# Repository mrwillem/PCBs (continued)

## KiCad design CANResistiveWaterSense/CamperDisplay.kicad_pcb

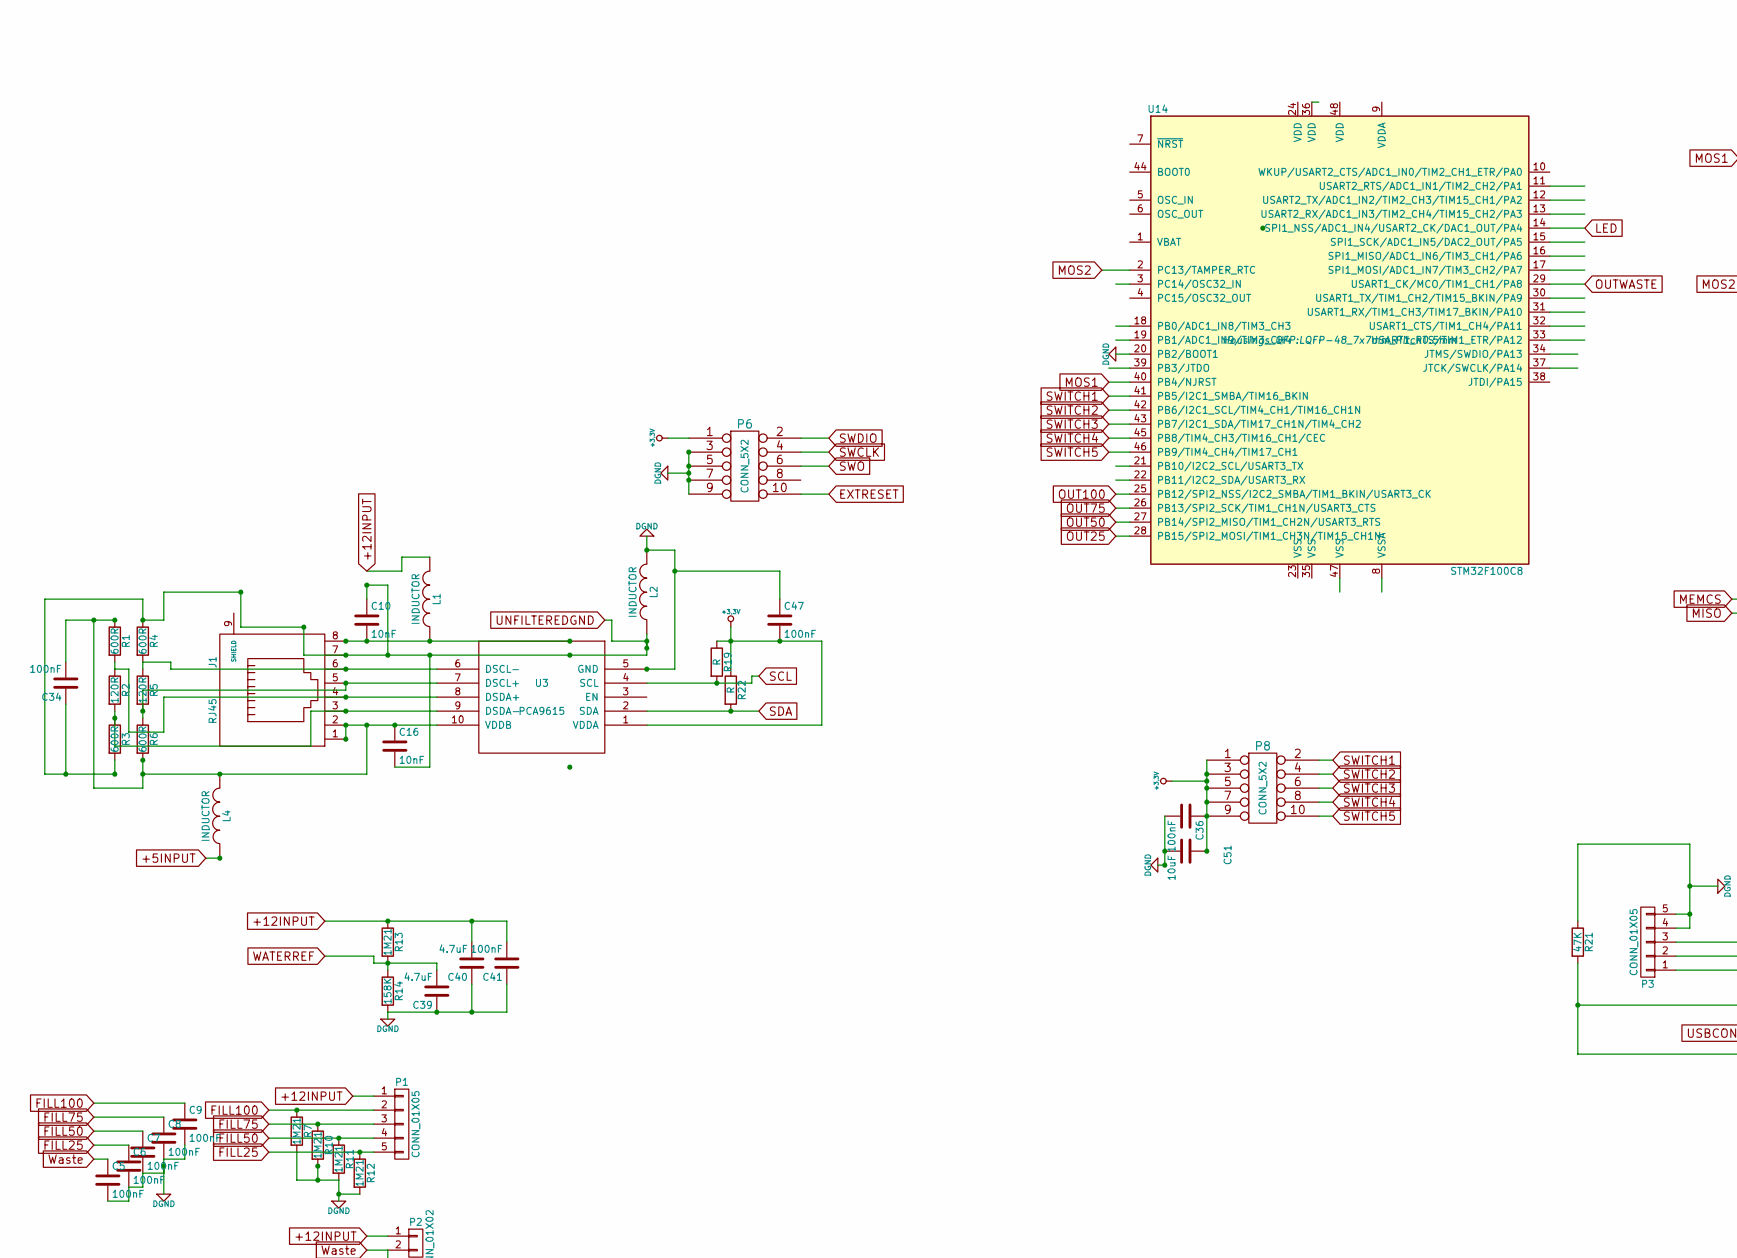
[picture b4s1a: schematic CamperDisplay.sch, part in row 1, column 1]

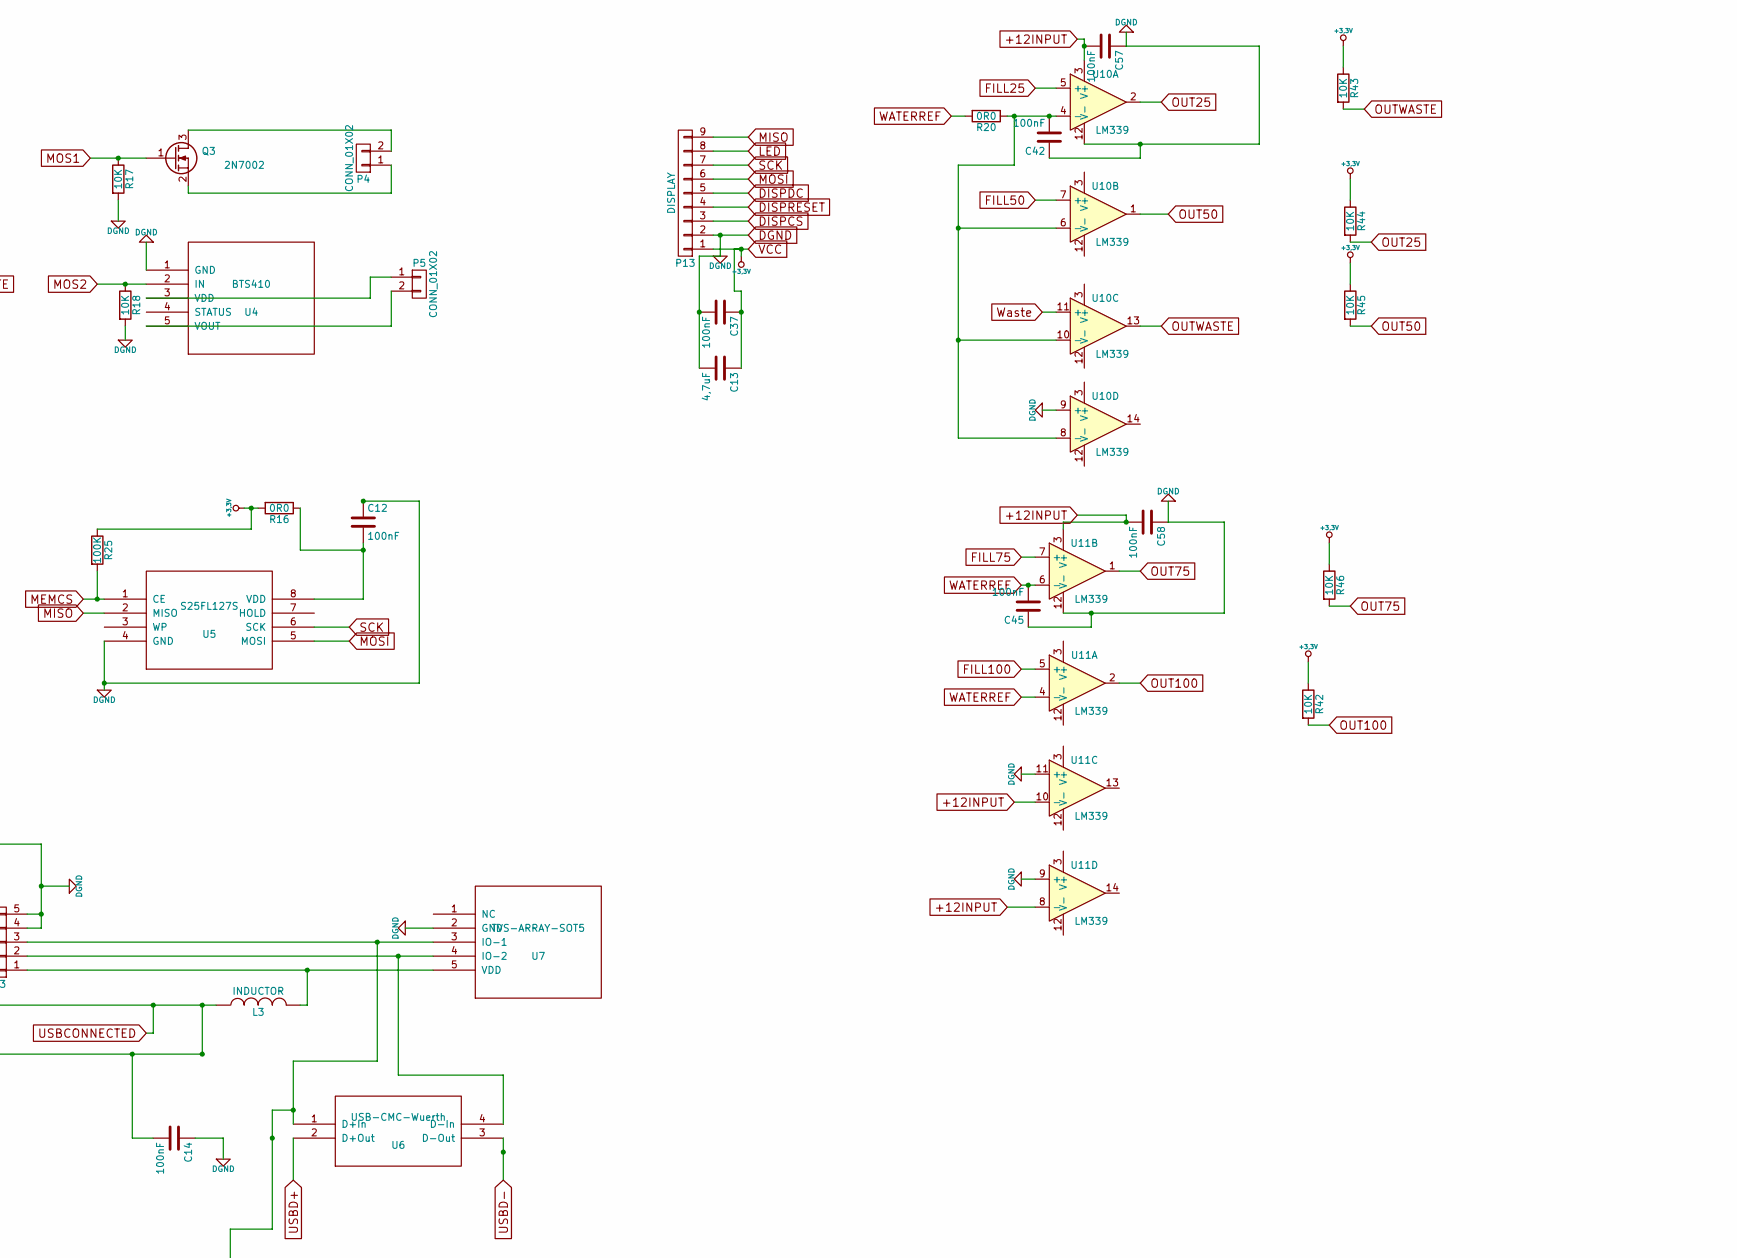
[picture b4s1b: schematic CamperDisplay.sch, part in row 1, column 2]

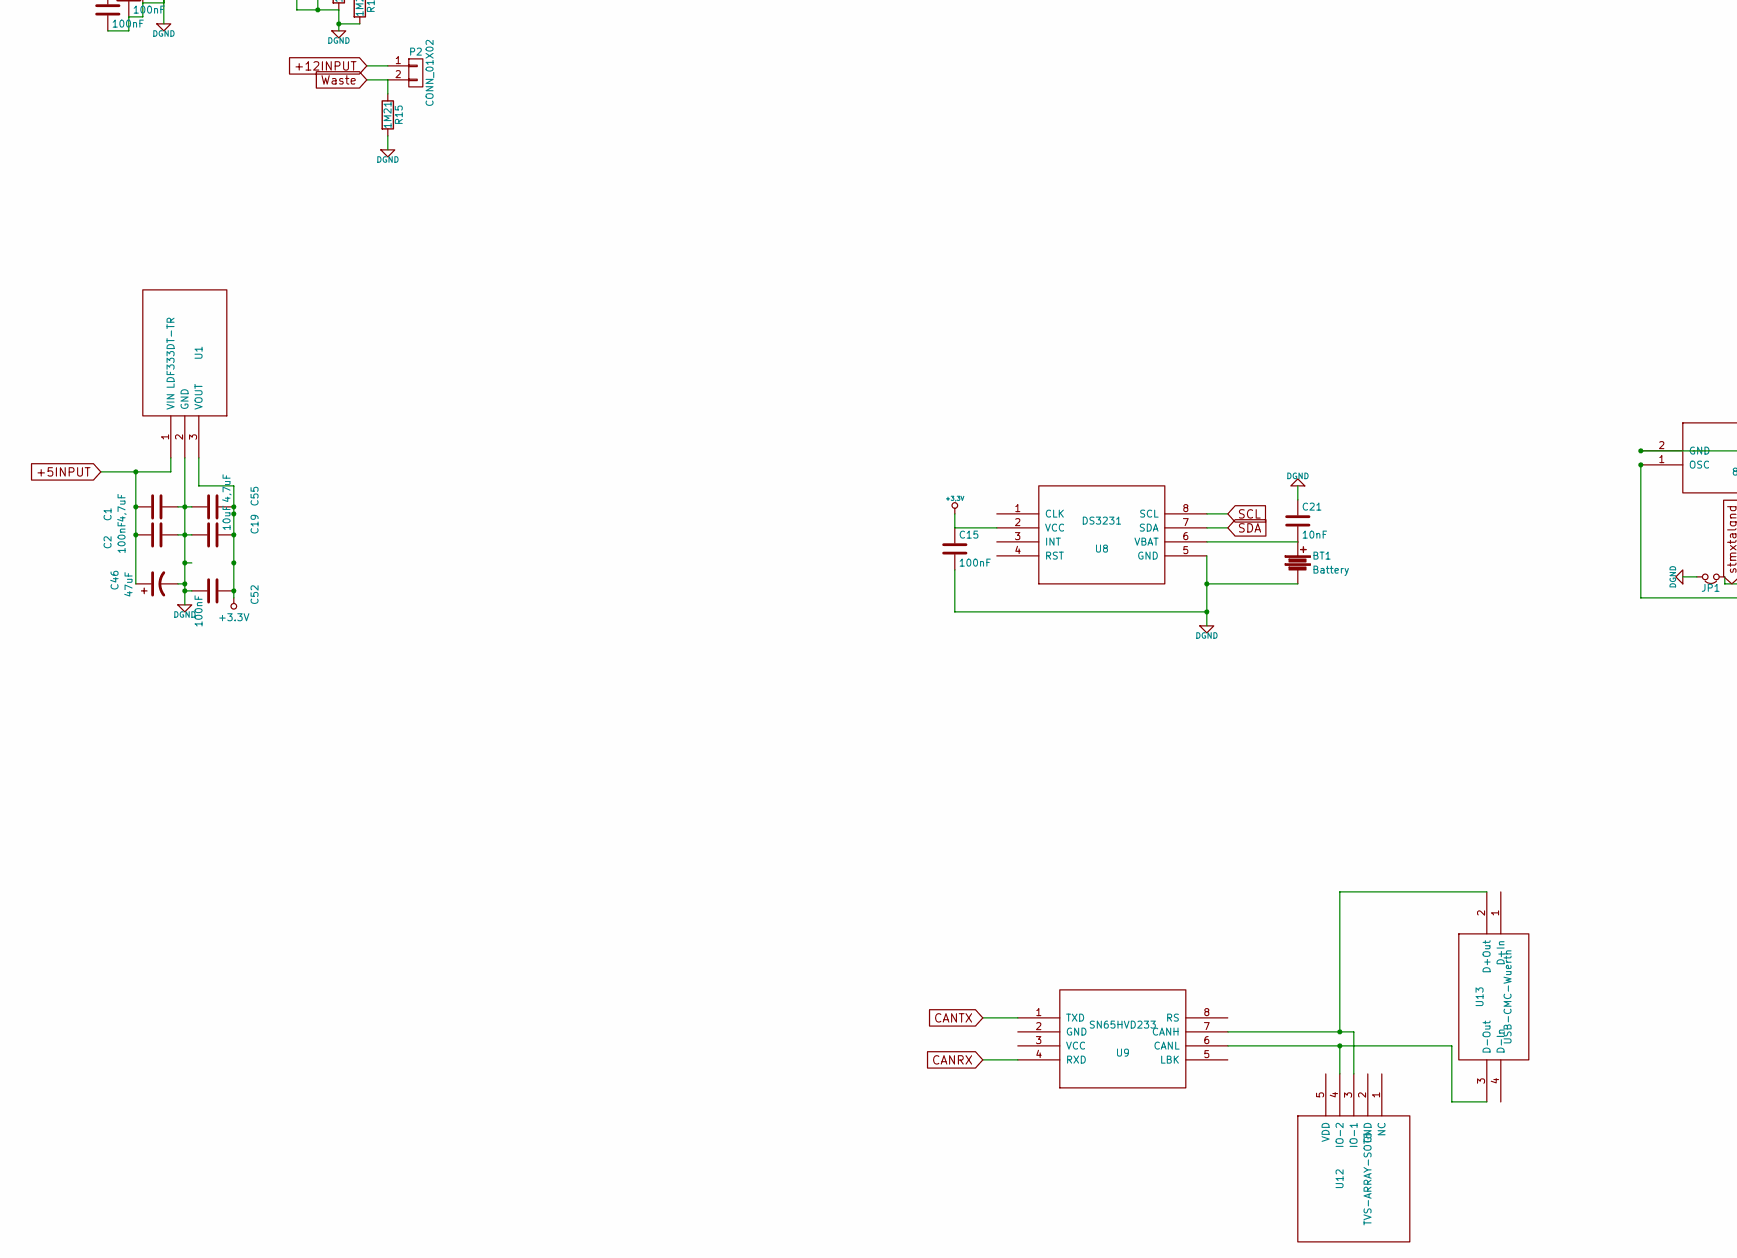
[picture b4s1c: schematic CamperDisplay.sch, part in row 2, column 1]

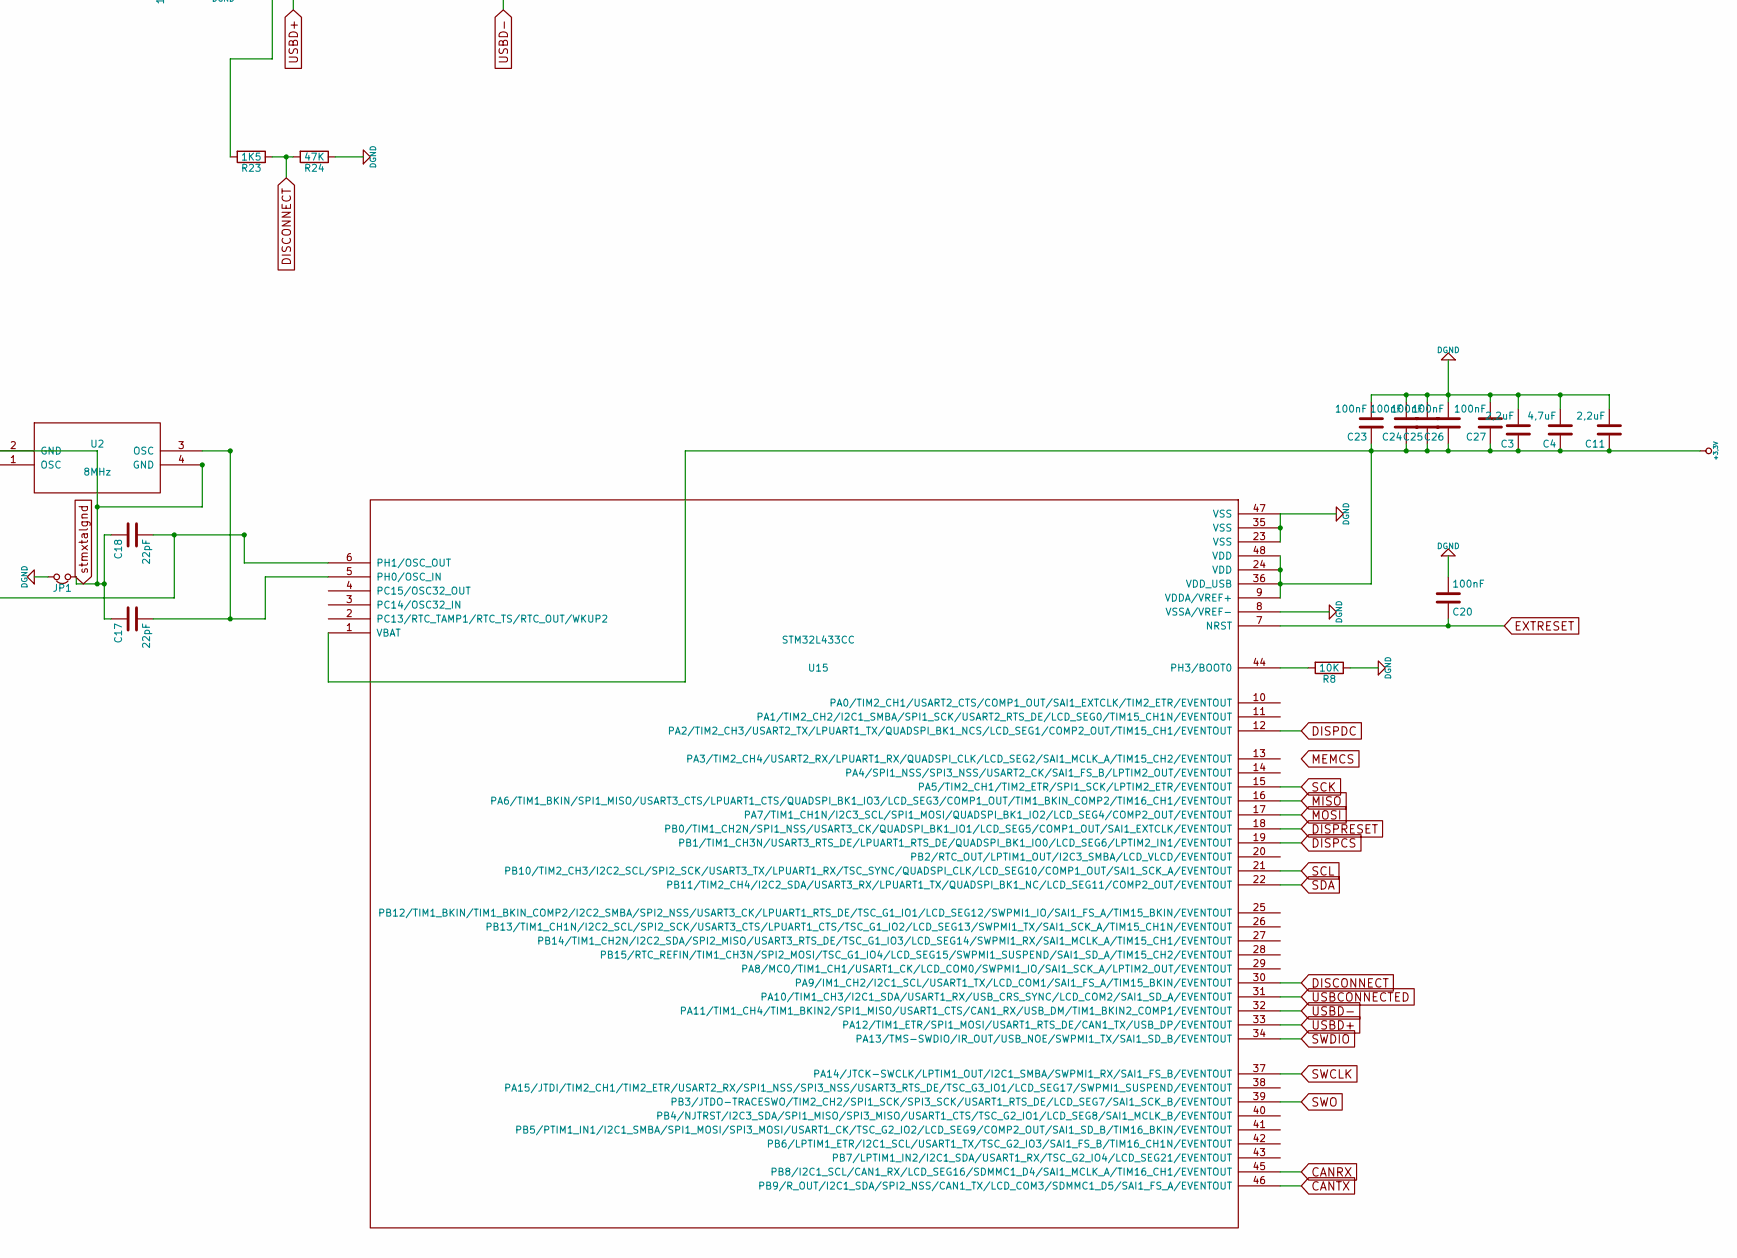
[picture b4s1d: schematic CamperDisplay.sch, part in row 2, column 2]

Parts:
BT1: Battery; BatterieHolderCR1025_SMD
C1, C4, C13, C55: 4,7uF; C_1206
C2, C5, C6, C7, C8, C9, C14, C15, C20, C23, C24, C25, C26, C27, C34, C36, C37, C41, C42, C45, C47, C52, C57, C58: 100nF; C_0805
C3: 2,2uF; C_0805
C10, C16, C21: 10nF; C_0805
C11: 2,2uF; C_1206
C12: 100nF; C_1206
C17, C18: 22pF; C_0805
C19, C51: 10uF; C_1206
C39, C40: 4.7uF; C_1206
C46: 47uF; c_elec_6.3x5.8
J1: RJ45; RJ45_8
JP1: Jumper_NC_Small; NetTie-I_Connected_SMD
L1, L2, L3, L4: INDUCTOR; C_0805_HandSoldering
P1: CONN_01X05; weidmueller_5
P2, P4, P5: CONN_01X02; weidmueller_2
P3: CONN_01X05; SMD_PIN_HEADER_01x05_angled
P6: CONN_5X2; Pin_Header_Straight_2x05_Pitch1.27mm
P8: CONN_5X2; weidmueller_10
P13: DISPLAY; 2.2inchQVGASPIwithStorage
Q3: 2N7002; SOT-23
R1, R3, R4, R6: 600R; R_0805_HandSoldering
R2, R5: 120R; R_0805_HandSoldering
R7, R10, R11, R12, R13, R15: 1M21; R_1206
R8, R17, R18, R42, R43, R44, R45, R46: 10K; R_0805_HandSoldering
R14: 158K; R_1206
R16, R20: 0R0; R_1206_HandSoldering
R19, R22: R; R_0805_HandSoldering
R21, R24: 47K; R_0603_HandSoldering
R23: 1K5; R_0603_HandSoldering
R25: 100K; R_0805_HandSoldering
U1: LDF333DT-TR; TO-252-2Lead
U2: 8MHz; Xtal_Ceramic_5x3.2
U3: PCA9615; TSSOP-10_3x3mm_Pitch0.5mm
U4: BTS410; TO-263-5Lead
U5: S25FL127S; SOIJ-8_5.3x5.3mm_Pitch1.27mm
U6, U13: USB-CMC-Wuerth; CMC-SMD-Wuerth
U7, U12: TVS-ARRAY-SOT5; SOT-23-5
U8: DS3231; SOIC-8_3.9x4.9mm_Pitch1.27mm
U9: SN65HVD233; SOIC-8_3.9x4.9mm_Pitch1.27mm
U10, U11: LM339; SOIC-14_3.9x8.7mm_Pitch1.27mm
U14: STM32F100C8; LQFP-48_7x7mm_Pitch0.5mm
U15: STM32L433CC; LQFP-48_7x7mm_Pitch0.5mm

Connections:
+5INPUT: C1.2, C2.2, C46.1, L4.1, U1.1 (VIN)
+12INPUT: C40.2, C41.2, C57.2, C58.2, L1.2, P1.1, P2.1, R13.1, U10.3 (V+), U11.3 (V+), U11.8 (-), U11.10 (-)
CANRX: U9.4 (RXD), U15.45 (PB8/I2C1_SCL/CAN1_RX/LCD_SEG16/SDMMC1_D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)
CANTX: U9.1 (TXD), U15.46 (PB9/R_OUT/I2C1_SDA/SPI2_NSS/CAN1_TX/LCD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)
DGND: BT1.2, C1.1, C2.1, C3.2, C4.2, C5.2, C6.2, C7.2, C8.2, C9.2, C11.2, C12.1, C13.2, C14.1, C15.2, C19.1, C20.2, C21.1, C23.2, C24.2, C25.2, C26.2, C27.2, C36.2, C37.2, C39.1, C40.1, C41.1, C42.1, C45.1, C46.2, C47.1, C51.2, C52.2, C55.1, C57.1, C58.1, JP1.1, L2.2, P3.4, P3.5, P6.3, P6.5, P6.7, P6.9, P13.2, R7.2, R8.1, R10.2, R11.2, R12.2, R14.2, R15.2, R17.2, R18.2, R21.1, R24.1, U1.2 (GND), U3.5 (GND), U4.1 (GND), U5.4 (GND), U7.2 (GND), U8.5 (GND), U10.9 (+), U10.12 (V-), U11.9 (+), U11.11 (+), U11.12 (V-), U14.20 (PB2/BOOT1), U15.8 (VSSA/VREF-), U15.23 (VSS), U15.35 (VSS), U15.47 (VSS)
DISCONNECT: R23.1, R24.2, U15.30 (PA9/IM1_CH2/I2C1_SCL/USART1_TX/LCD_COM1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)
DISPCS: P13.3, U15.19 (PB1/TIM1_CH3N/USART3_RTS_DE/LPUART1_RTS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)
DISPDC: P13.5, U15.12 (PA2/TIM2_CH3/USART2_TX/LPUART1_TX/QUADS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)
DISPRESET: P13.4, U15.18 (PB0/TIM1_CH2N/SPI1_NSS/USART3_CK/QUADSP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)
EXTRESET: C20.1, P6.10, U15.7 (NRST)
FILL25: C6.1, P1.5, R12.1, U10.5 (+)
FILL50: C7.1, P1.4, R11.1, U10.7 (+)
FILL75: C8.1, P1.3, R10.1, U11.7 (+)
FILL100: C9.1, P1.2, R7.1, U11.5 (+)
LED: P13.8, U14.14 (SPI1_NSS/ADC1_IN4/USART2_CK/DAC1_OUT/PA4)
MEMCS: R25.2, U5.1 (CE)
MISO: P13.9, U5.2 (MISO), U15.16 (PA6/TIM1_BKIN/SPI1_MISO/USART3_CTS/LPUA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)
MOS1: Q3.1 (G), R17.1, U14.40 (PB4/NJRST)
MOS2: R18.1, U4.2 (IN), U14.2 (PC13/TAMPER_RTC)
MOSI: P13.6, U5.5 (MOSI), U15.17 (PA7/TIM1_CH1N/I2C3_SCL/SPI1_MOSI/QUADSP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)
unnamed: BT1.1, C21.2, U8.6 (VBAT)
unnamed: C10.2, J1.8, L1.1
unnamed: C12.2, R16.1, U5.8 (VDD)
unnamed: C16.1, C34.2, J1.1, J1.2, L4.2, R1.1, R6.2, U3.10 (VDDB)
unnamed: C17.2, U2.3 (OSC), U15.5 (PH0/OSC_IN)
unnamed 25: C18.2, U2.1 (OSC), U15.6 (PH1/OSC_OUT); also elsewhere on the board
unnamed: C42.2, R20.1, U10.4 (-), U10.6 (-), U10.8 (-), U10.10 (-)
unnamed: J1.3, R2.2, R3.1, U3.9 (DSDA-)
unnamed: J1.4, R1.2, R2.1, U3.8 (DSDA+)
unnamed: J1.5, R5.2, R6.1, U3.7 (DSCL+)
unnamed: J1.6, R4.2, R5.1, U3.6 (DSCL-)
unnamed: L3.2, P3.1, U7.5 (VDD)
unnamed: P3.2, U6.4 (D-In), U7.4 (IO-2)
unnamed: P3.3, R23.2, U6.1 (D+In), U7.3 (IO-1)
unnamed: P4.1, Q3.2 (S)
unnamed: P4.2, Q3.3 (D)
unnamed: P5.1, U4.3 (VDD)
unnamed: P5.2, U4.5 (VOUT)
unnamed: R8.2, U15.44 (PH3/BOOT0)
unnamed: U9.7 (CANH), U12.3 (IO-1), U13.2 (D+Out)
unnamed: U9.6 (CANL), U12.4 (IO-2), U13.3 (D-Out)
OUT25: R44.2, U10.2, U14.28 (PB15/SPI2_MOSI/TIM1_CH3N/TIM15_CH1N)
OUT50: R45.2, U10.1, U14.27 (PB14/SPI2_MISO/TIM1_CH2N/USART3_RTS)
OUT75: R46.2, U11.1, U14.26 (PB13/SPI2_SCK/TIM1_CH1N/USART3_CTS)
OUT100: R42.2, U11.2, U14.25 (PB12/SPI2_NSS/I2C2_SMBA/TIM1_BKIN/USART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)
OUTWASTE: R43.2, U10.13, U14.29 (USART1_CK/MCO/TIM1_CH1/PA8)
SCK: P13.7, U5.6 (SCK), U15.15 (PA5/TIM2_CH1/TIM2_ETR/SPI1_SCK/LPTIM2_E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)
SCL: R19.2, U3.4 (SCL), U8.8 (SCL), U15.21 (PB10/TIM2_CH3/I2C2_SCL/SPI2_SCK/USART3_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)
SDA: R22.2, U3.2 (SDA), U8.7 (SDA), U15.22 (PB11/TIM2_CH4/I2C2_SDA/USART3_RX/LPUART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)
SWCLK: P6.4, U15.37 (PA14/JTCK-SWCLK/LPTIM1_OUT/I2C1_SMBA/SW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)
SWDIO: P6.2, U15.34 (PA13/TMS-SWDIO/IR_OUT/USB_NOE/SWPMI1_TX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)
SWITCH1: P8.2, U14.41 (PB5/I2C1_SMBA/TIM16_BKIN)
SWITCH2: P8.4, U14.42 (PB6/I2C1_SCL/TIM4_CH1/TIM16_CH1N)
SWITCH3: P8.6, U14.43 (PB7/I2C1_SDA/TIM17_CH1N/TIM4_CH2)
SWITCH4: P8.8, U14.45 (PB8/TIM4_CH3/TIM16_CH1/CEC)
SWITCH5: P8.10, U14.46 (PB9/TIM4_CH4/TIM17_CH1)
SWO: P6.6, U15.39 (PB3/JTDO-TRACESWO/TIM2_CH2/SPI1_SCK/SPI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)
UNFILTEREDGND: C10.1, C16.2, C34.1, J1.7, L2.1, R3.2, R4.1
USBCONNECTED: C14.2, L3.1, R21.2, U15.31 (PA10/TIM1_CH3/I2C1_SDA/USART1_RX/USB_CR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)
USBD+: U6.2 (D+Out), U15.33 (PA12/TIM1_ETR/SPI1_MOSI/USART1_RTS_DE/C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)
USBD-: U6.3 (D-Out), U15.32 (PA11/TIM1_CH4/TIM1_BKIN2/SPI1_MISO/USAR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)
WATERREF: C39.2, C45.2, R13.2, R14.1, R20.2, U11.4 (-), U11.6 (-)
Waste: C5.1, P2.2, R15.1, U10.11 (+)
stmxtalgnd: C17.1, C18.1, JP1.2, U2.2 (GND), U2.4 (GND)

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
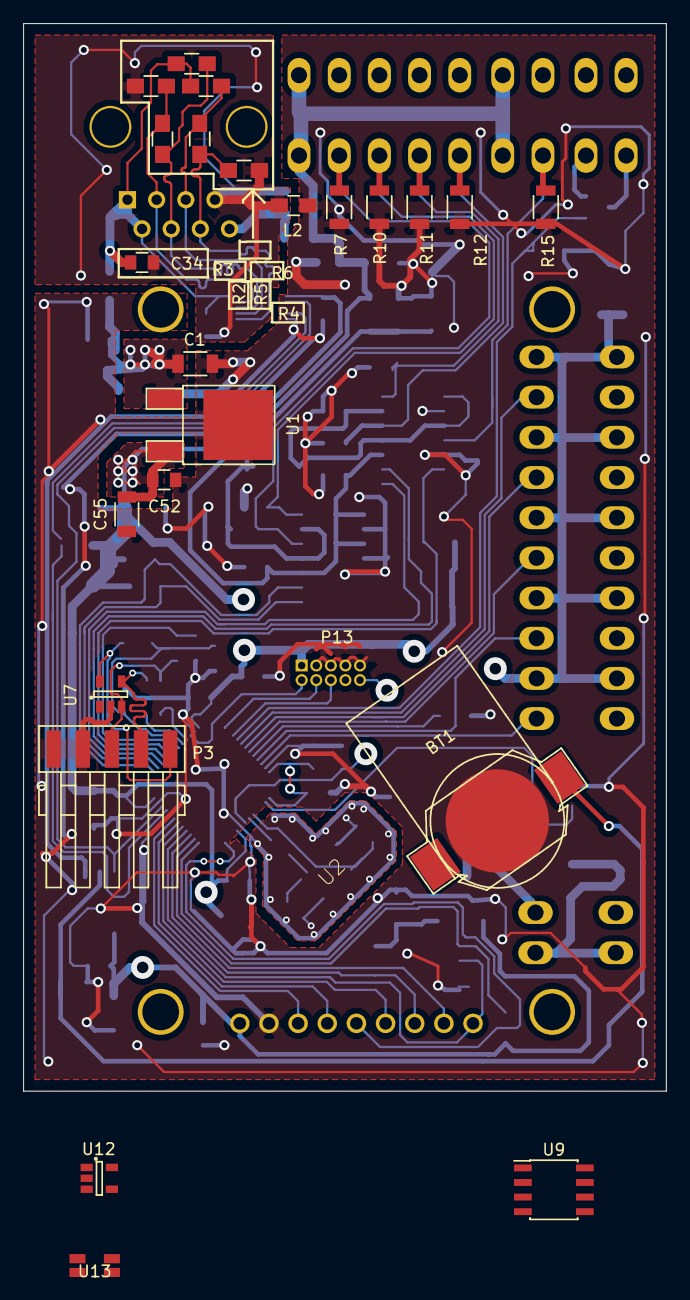
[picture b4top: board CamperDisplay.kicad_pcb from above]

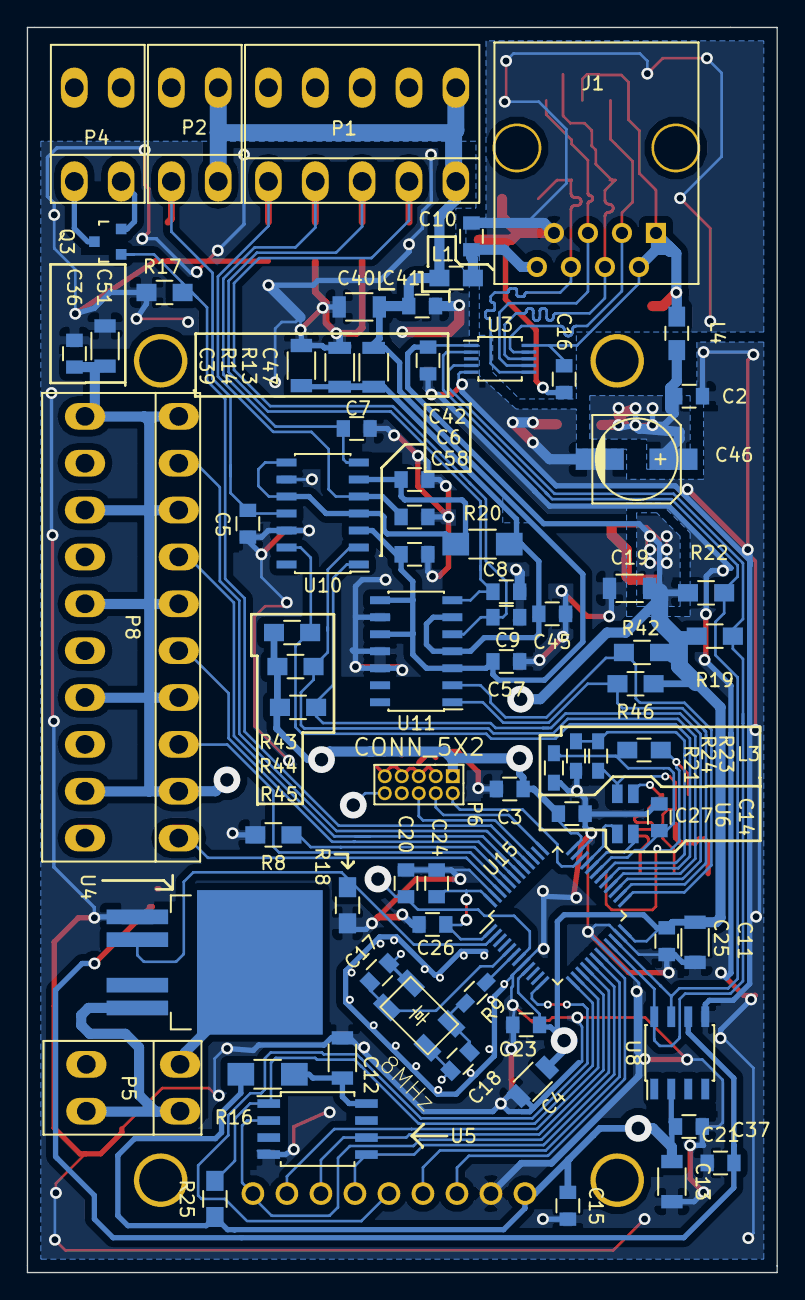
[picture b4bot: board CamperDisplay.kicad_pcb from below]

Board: 4 copper layers, 56.0 x 93.0 mm, 101 parts (77 on the bottom side), 59 nets.

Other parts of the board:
R9: ???; R_0603_HandSoldering

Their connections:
unnamed 25: R9.2; also elsewhere on the board

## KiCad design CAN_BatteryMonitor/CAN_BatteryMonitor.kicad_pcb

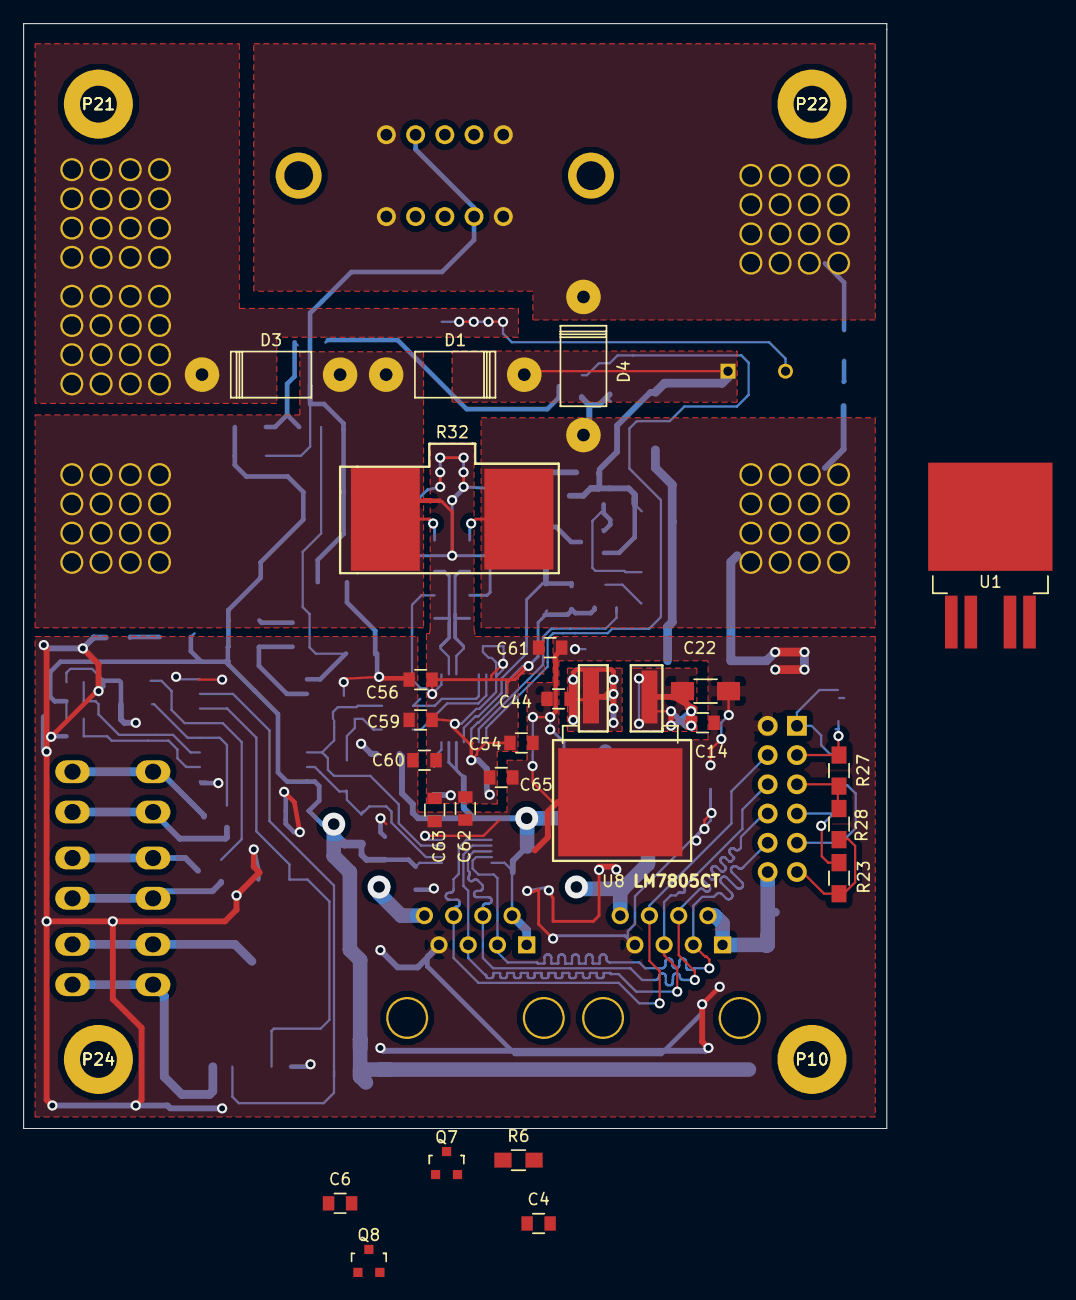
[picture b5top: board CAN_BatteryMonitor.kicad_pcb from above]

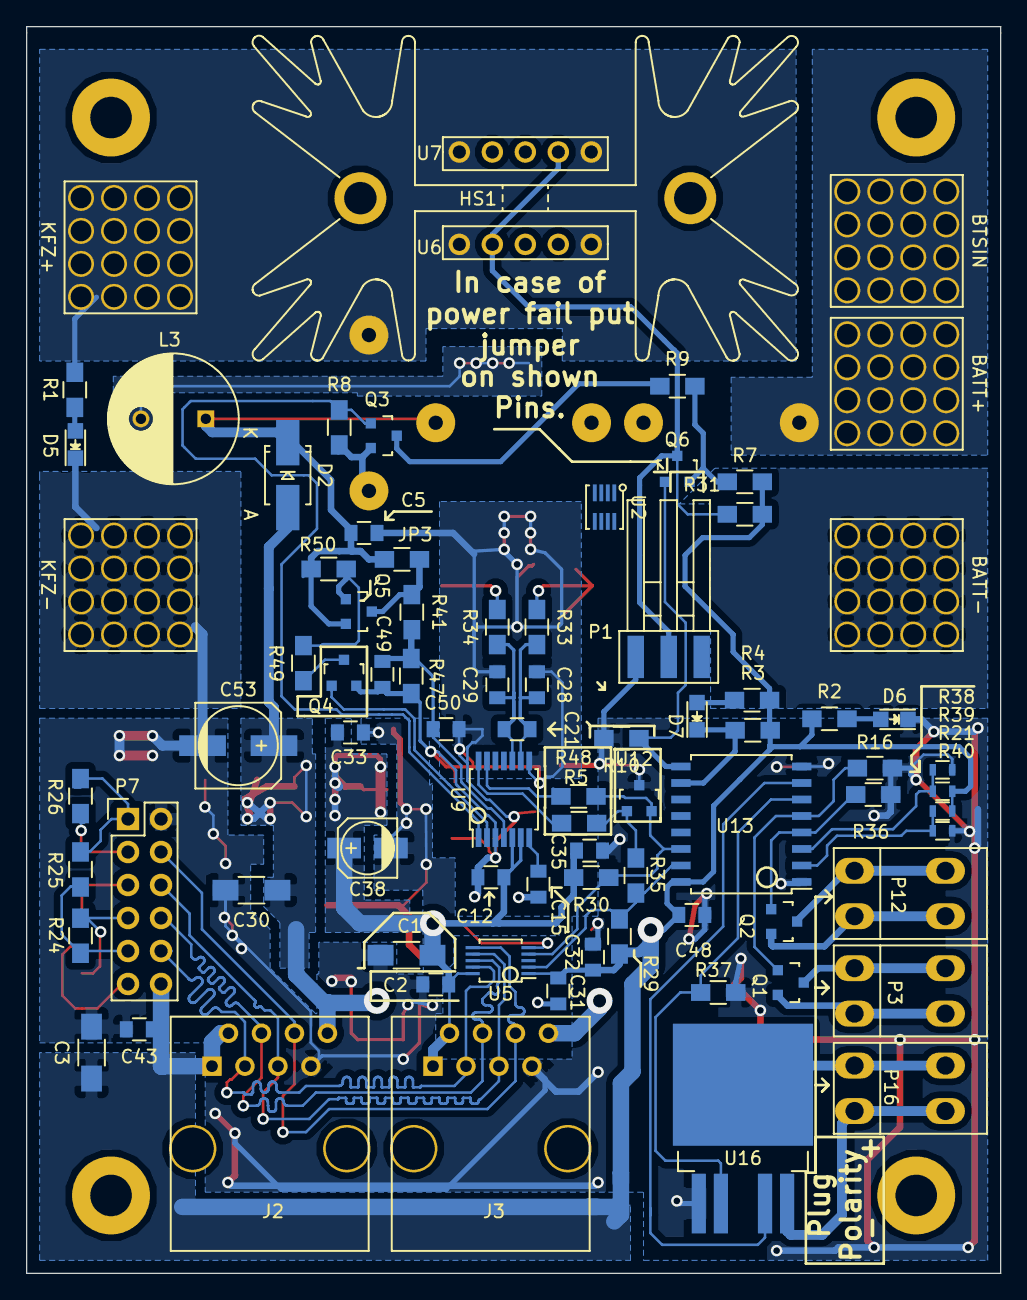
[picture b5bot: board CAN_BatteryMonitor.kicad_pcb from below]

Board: 4 copper layers, 75.0 x 96.0 mm, 113 parts (83 on the bottom side), 55 nets.

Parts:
BATT+1: BATT+; WE_threaded_shank_M5_160A
BATT-1: BATT-; WE_threaded_shank_M5_160A
BTSIN1: BTSIN; WE_threaded_shank_M5_160A
C1, C3: 4.7uF; C_1206_HandSoldering
C2, C5, C12, C14, C21, C28, C29, C31, C32, C35, C43, C48, C49, C54, C56, C59, C60, C61, C62, C63, C65: 100nF; C_0805
C4, C6, C15, C33: 1uF; C_0805
C22: 4,7uF; C_1206_HandSoldering
C30: 10uF; C_1206_HandSoldering
C38: 10uF; c_elec_4x5.8
C44: 10nF; C_0805
C50: 3,3nF; C_0805
C53: 100uF; c_elec_6.3x7.7
D1, D3, D4: P6KE16CA; Diode_DO-201AC_Horizontal_RM12
D2: DIODE; SMA_Handsoldering
D5: BLUE; LED_0805
D6: RED; LED_0805
D7: GREEN; LED_0805
HS1: HEATSINK; Heatsink_Fischer_SK129-STS_42x25mm_2xDrill2.5mm
J2, J3: RJ45; RJ45_8
JP2: Jumper_NC_Small; NetTie0.4mmSMD
JP3: Jumper_NO_Small; R_0805_HandSoldering
KFZ+1: KFZ+; WE_threaded_shank_M5_160A
KFZ-1: KFZ-; WE_threaded_shank_M5_160A
L3: TSL0808-470K1R2; C_Radial_D10_L16_P5
P1: CONN_01X03; SMD_PIN_HEADER_01x03_angled
P3, P12, P16: CONN_01X02; weidmueller_2
P7: CONN_02X06; Pin_Header_Straight_2x06
P10: P10; hole
P21: P21; hole
P22: P22; hole
P24: P24; hole
Q1, Q2, Q3, Q4, Q6, Q7: 2N7002; SOT-23
Q5, Q8: BSS84; SOT-23
R1: 680R; R_0805_HandSoldering
R2, R4: 220R; R_0805_HandSoldering
R3, R50: 100K; R_0805_HandSoldering
R5, R33, R34, R48: 100R; R_0805_HandSoldering
R6, R7, R8, R10, R16, R31, R36, R37: 10K; R_0805_HandSoldering
R9, R35: 0R0; R_0805_HandSoldering
R21, R38, R39, R40: 0R0; R_0603
R23, R25, R26, R28: 600R; R_0805_HandSoldering
R24, R27: 120R; R_0805_HandSoldering
R29, R30: 4K7; R_0805_HandSoldering
R32: 0.0002R; WSLP_5931_DALE
R41: 300K; R_0805_HandSoldering
R47: 16K5; R_0805_HandSoldering
R49: 169K; R_0805_HandSoldering
U1, U16: BTS410; TO-263-4Lead
U2: LT3009; SC70-8
U5: PCA9615; TSSOP-10_3x3mm_Pitch0.5mm
U6, U7: BTS555; TO218-5
U8: LM7805CT; TO-263-2Lead
U9: BQ34Z100-G1; TSSOP-14_4.4x5mm_Pitch0.65mm
U12: AZ23c5v6; SOT-23
U13: PCA9534; SOIC-16_7.5x10.3mm_Pitch1.27mm

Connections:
+3V3: C6.2, C12.1, U2.6, U9.5, U9.6
+5V: C1.1, C2.1, C3.1, C31.1, C32.1, C33.1, C35.1, C38.1, C43.1, C44.1, C48.1, J2.1, J2.2, J3.1, J3.2, P7.12, R2.1, R3.1, R4.1, R7.1, R21.1, R29.2, R30.2, R31.1, R38.2, U5.1, U5.10, U8.3, U13.16
ALARM: Q3.1, Q7.1, R6.2, R8.2, U9.1
BATSENSE: C49.1, C50.1, R41.2, R47.1, U9.4
BATT+: BATT+1.1, BTSIN1.1, D3.1, L3.2, U6.3, U7.3
BATT-: BATT-1.1, D1.2, D3.2, JP2.2, R32.1, R33.1
BTS_CTRL_SIGNAL: P1.2, Q6.3, R31.2, U6.2, U7.2
BTS_MCU_SIGNAL: Q6.1, R10.1, U13.9
CALVINSHIELD: C4.2, C5.2, C6.1, C12.2, C15.2, C28.1, C29.2, C49.2, C50.2, C54.2, C56.2, C59.2, C60.2, C61.2, C62.2, C63.2, C65.2, JP2.1, Q4.2, R47.2, U2.2, U2.3, U2.4, U9.3, U9.8
KFZ-: C1.2, C2.2, C3.2, C14.2, C22.2, C30.2, C31.2, C32.2, C33.2, C35.2, C38.2, C43.2, C44.2, C48.2, C53.2, C54.1, C56.1, C59.1, C60.1, C61.1, C62.1, C63.1, C65.1, D4.2, D5.1, D6.1, J2.7, J3.7, KFZ-1.1, P1.1, P7.2, Q3.2, Q7.2, R6.1, R8.1, R10.2, R16.2, R32.2, R34.2, R36.2, R37.2, R39.1, R40.1, U1.1, U5.5, U8.2, U12.3, U13.1, U13.8, U16.1
KFZOUT: D4.1, KFZ+1.1, R1.1, U6.1, U6.5, U7.1, U7.5
unnamed: C4.1, U2.1, U2.5
unnamed: C15.1, U9.7
unnamed: C21.1, C28.2, R33.2, U9.9
unnamed: C21.2, C29.1, R34.1, U9.10
unnamed: D5.2, R1.2
unnamed: D6.2, R2.2
unnamed: D7.1, R3.2, U13.10
unnamed: D7.2, R4.2
unnamed: J2.3, J3.3, P7.10, U5.9
unnamed: J2.4, J3.4, P7.8, U5.8
unnamed: J2.5, J3.5, P7.6, U5.7
unnamed: J2.6, J3.6, P7.4, U5.6
unnamed: JP3.2, Q5.3, R41.1
unnamed: P3.1, Q1.2
unnamed: P3.2, Q1.3
unnamed: P7.1, R25.2, R26.1
unnamed: P7.3, R26.2, R27.1
unnamed: P7.5, R27.2, R28.1
unnamed: P7.7, R23.2, R24.1
unnamed: P7.9, R24.2, R25.1
unnamed: P7.11, R23.1, R28.2
unnamed: P12.1, Q2.2
unnamed: P12.2, Q2.3
unnamed: P16.1, U16.5
unnamed: P16.2, U16.3
unnamed: Q1.1, R16.1, U13.5
unnamed: Q2.1, R36.1, U13.4
unnamed: Q3.3, R9.1
unnamed: Q4.3, R49.1
unnamed: Q5.1, R49.2, R50.1
unnamed: Q6.2, R7.2, R9.2
unnamed: R5.2, U9.14
unnamed: R21.2, R40.2, U13.2
unnamed: R5.1, R35.2, U12.1
unnamed: R37.1, U13.6, U16.2
unnamed: R38.1, R39.2, U13.3
unnamed: R48.2, U9.13
unnamed: U13.7, U16.4
POSTDIODE: D2.2, U1.3
PREDIODE: C5.1, D1.1, D2.1, JP3.1, L3.1, Q5.2, R50.2
SCL2: R30.1, R48.1, U5.4, U12.2, U13.14
SDA2: R29.1, R35.1, U5.2, U13.15
SENSE_ENABLE: Q4.1, U9.2
VREGIN: C14.1, C22.1, C30.1, C53.1, J2.8, J3.8, U1.5, U8.1
